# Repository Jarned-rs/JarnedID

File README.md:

# T-Pad
- The T-Pad is a basic telemetry module that will track different metrics using 4 main sensors and then send those metrics to a web dashboard. I made this project as an intro into sensors to use as reference to future projects with sensors and data being fed back to a main dashboard.

# How it works
- The board's brain is a RP2040 Zero that will then send info back to the computer via USB. The board features the following:
  -   A BME280 to track temperature and humidity
  -   A RP2040 as the brain
  -   An INA 219 to track voltage supply
  -   BH1750 to track light intensity
  -   A BMI 270 as a gyroscope and accelerometer

# Photos
Schematic:

PCB:

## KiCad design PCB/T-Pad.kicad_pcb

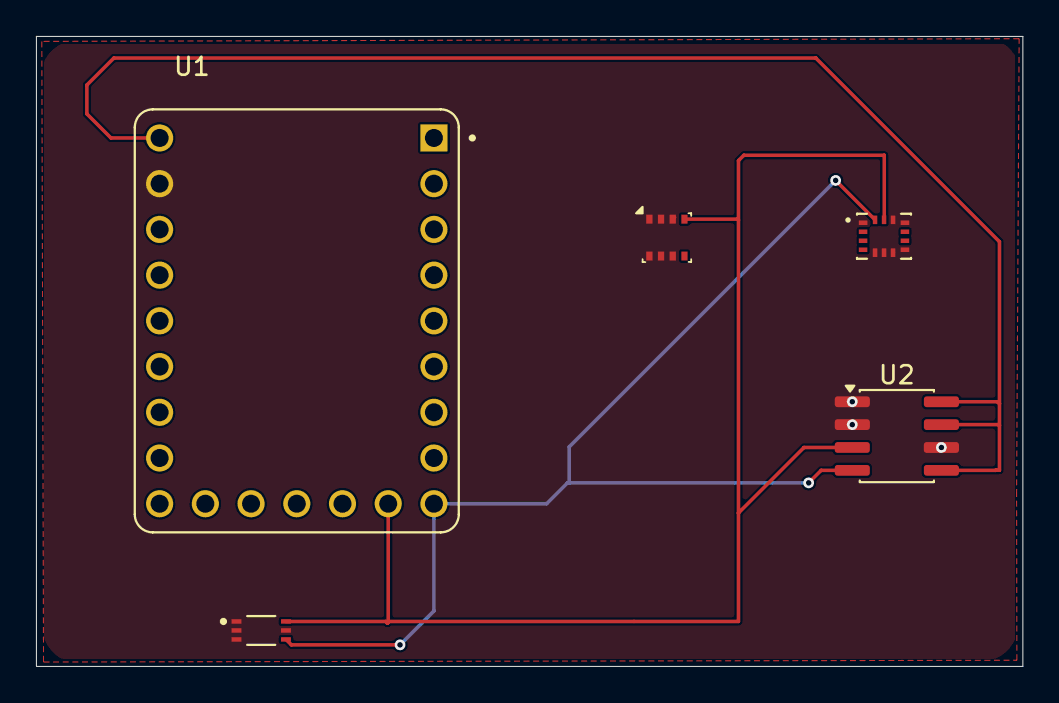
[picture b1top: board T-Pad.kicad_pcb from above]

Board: 2 copper layers, 54.8 x 35.0 mm, 5 parts (0 on the bottom side), 4 nets.

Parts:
U1: RP2040-ZERO; MODULE_RP2040-ZERO
U2: INA219AxD; SOIC-8_3.9x4.9mm_P1.27mm
U4: BME280; Bosch_LGA-8_2.5x2.5mm_P0.65mm_ClockwisePinNumbering
U5: BH1750FVI-TR; XDCR_BH1750FVI-TR
U6: BMI270; XDCR_BMI270

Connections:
+5V: U1.23 (5V), U2.5 (VS), U2.7 (IN-), U2.8 (IN+)
GND: U1.22 (GND), U2.1 (A1), U2.2 (A0), U2.6 (GND), U4.1 (GND), U4.2 (CSB), U4.3 (SDI), U4.6 (VDDIO), U4.7 (GND), U4.8 (VDD), U5.1 (VCC), U5.2 (ADDR), U5.3 (GND), U5.5 (DVI), U6.1 (SDO), U6.5 (VDDIO), U6.6 (GNDIO), U6.7 (GND), U6.8 (VDD), U6.11 (OSDO), U6.12 (CSB)
unnamed: U1.9 (GP8), U2.4 (SCL), U5.4 (SDA), U6.14 (SDX)
unnamed: U1.10 (GP9), U2.3 (SDA), U4.4 (SCK), U5.6 (SCL), U6.13 (SCX)
